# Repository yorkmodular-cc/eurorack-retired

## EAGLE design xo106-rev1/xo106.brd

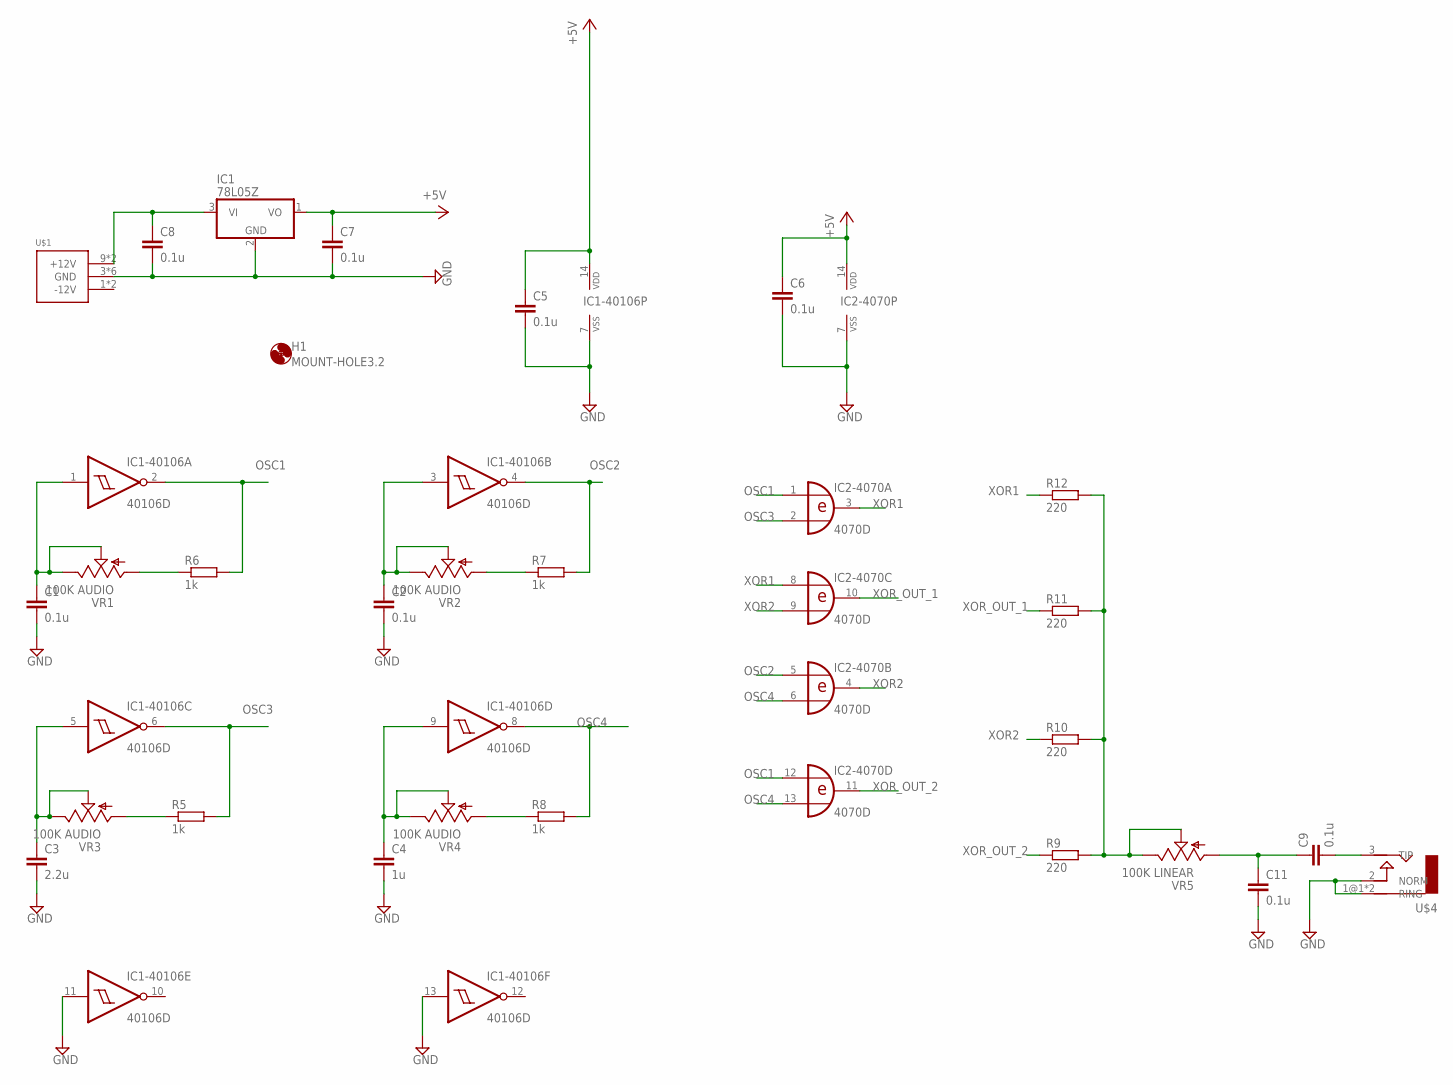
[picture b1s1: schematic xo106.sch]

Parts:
C1, C2, C5, C6, C7, C8, C9: 0.1u; C0805
C3: 2.2u; C0805
C4: 1u; C0805
C11: 0.1u; C050-025X075
H1: MOUNT-HOLE3.2; 3,2
IC1: 78L05Z; TO92
IC1-40106: 40106D; SO14
IC2-4070: 4070D; SO14
R5, R6, R7, R8: 1k; R0805
R9, R10, R12: 220; R0805
R11: 220; M0805
U$1: POWER_SIMPLE10; POWER_10
U$4: AUDIO-JACKERTHENVAR; ERTHENVAR-JACK
VR1, VR2, VR3, VR4: 100K AUDIO; 9MM_SNAP-IN_POT
VR5: 100K LINEAR; 9MM_SNAP-IN_POT

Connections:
+5V: C5.1, C6.1, C7.1, IC1.1 (VO), IC1-40106.14 (VDD), IC2-4070.14 (VDD)
GND: C1.2, C2.2, C3.2, C4.2, C5.2, C6.2, C7.2, C8.2, C11.2, IC1.2 (GND), IC1-40106.7 (VSS), IC1-40106.11 (I), IC1-40106.13 (I), IC2-4070.7 (VSS), U$1.3 (GND), U$1.4 (GND), U$1.5 (GND), U$1.6 (GND), U$1.7 (GND), U$1.8 (GND), U$4.1@1 (RING), U$4.1@2 (RING), U$4.2 (NORM)
unnamed: C9.1, C11.1, VR5.1 (A)
unnamed: R6.1, VR1.1 (A)
unnamed: R5.1, VR3.1 (A)
unnamed: R8.1, VR4.1 (A)
unnamed: C1.1, IC1-40106.1 (I), VR1.2 (S), VR1.3 (E)
unnamed: C2.1, IC1-40106.3 (I), VR2.2 (S), VR2.3 (E)
unnamed: C3.1, IC1-40106.5 (I), VR3.2 (S), VR3.3 (E)
unnamed: C4.1, IC1-40106.9 (I), VR4.2 (S), VR4.3 (E)
unnamed: R7.1, VR2.1 (A)
unnamed: C8.1, IC1.3 (VI), U$1.9 (+12V), U$1.10 (+12V)
unnamed: C9.2, U$4.3 (TIP)
unnamed: R9.2, R10.2, R11.2, R12.2, VR5.2 (S), VR5.3 (E)
OSC1: IC1-40106.2 (O), IC2-4070.1 (I0), IC2-4070.12 (I0), R6.2
OSC2: IC1-40106.4 (O), IC2-4070.5 (I0), R7.2
OSC3: IC1-40106.6 (O), IC2-4070.2 (I1), R5.2
OSC4: IC1-40106.8 (O), IC2-4070.6 (I1), IC2-4070.13 (I1), R8.2
XOR1: IC2-4070.3 (O), IC2-4070.8 (I0), R12.1
XOR2: IC2-4070.4 (O), IC2-4070.9 (I1), R10.1
XOR_OUT_1: IC2-4070.10 (O), R11.1
XOR_OUT_2: IC2-4070.11 (O), R9.1

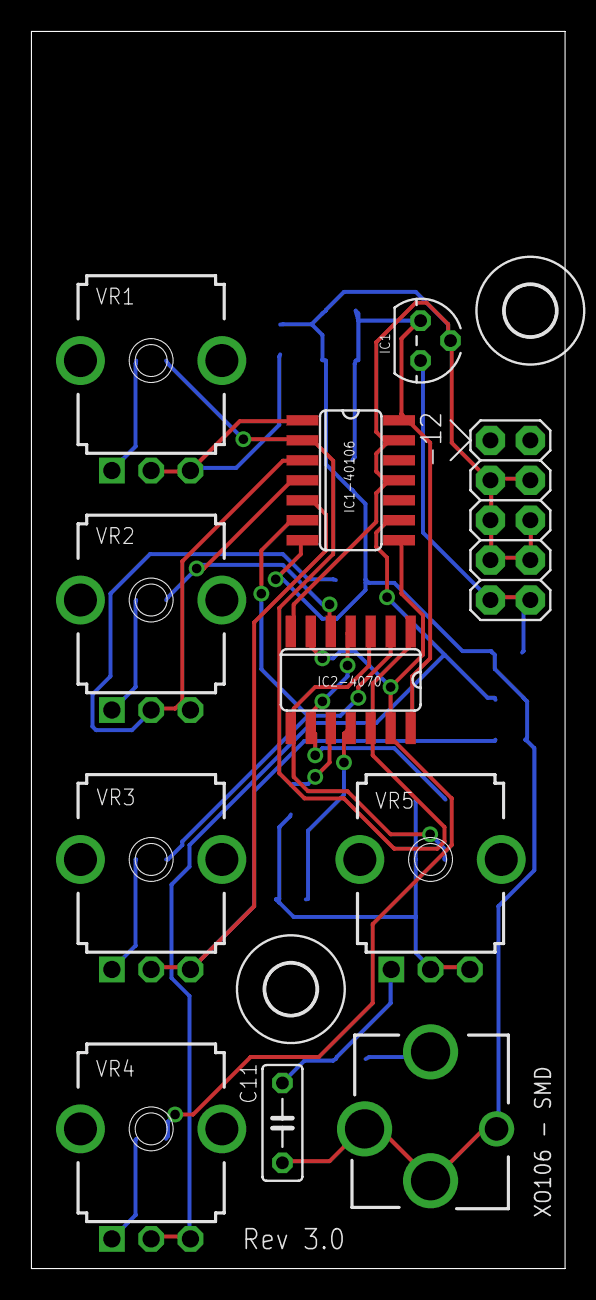
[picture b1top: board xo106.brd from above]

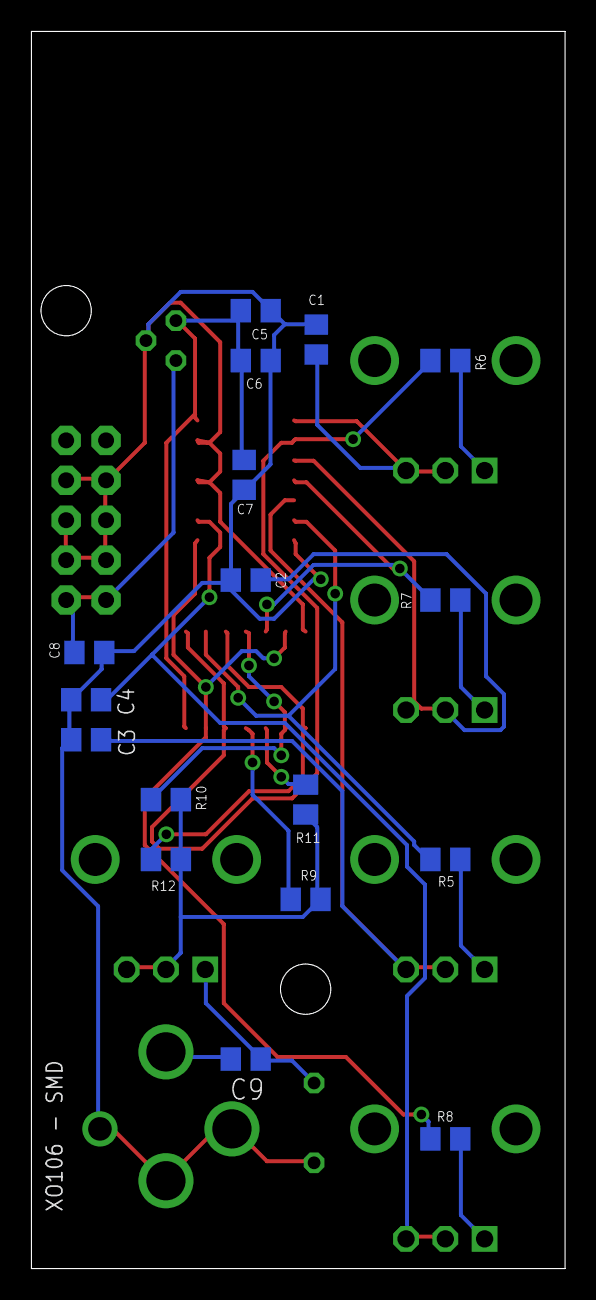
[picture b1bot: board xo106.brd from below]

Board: 2 copper layers, 34.0 x 78.7 mm, 30 parts (17 on the bottom side), 22 nets.

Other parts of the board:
H2: MOUNT-HOLE3.2; 3,2
